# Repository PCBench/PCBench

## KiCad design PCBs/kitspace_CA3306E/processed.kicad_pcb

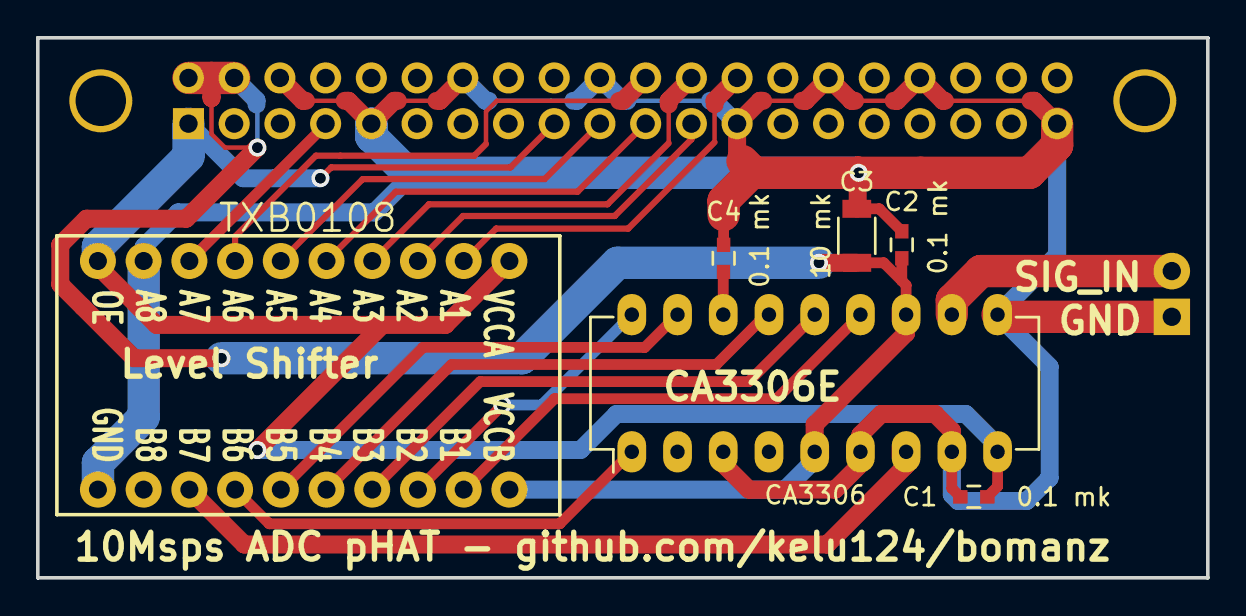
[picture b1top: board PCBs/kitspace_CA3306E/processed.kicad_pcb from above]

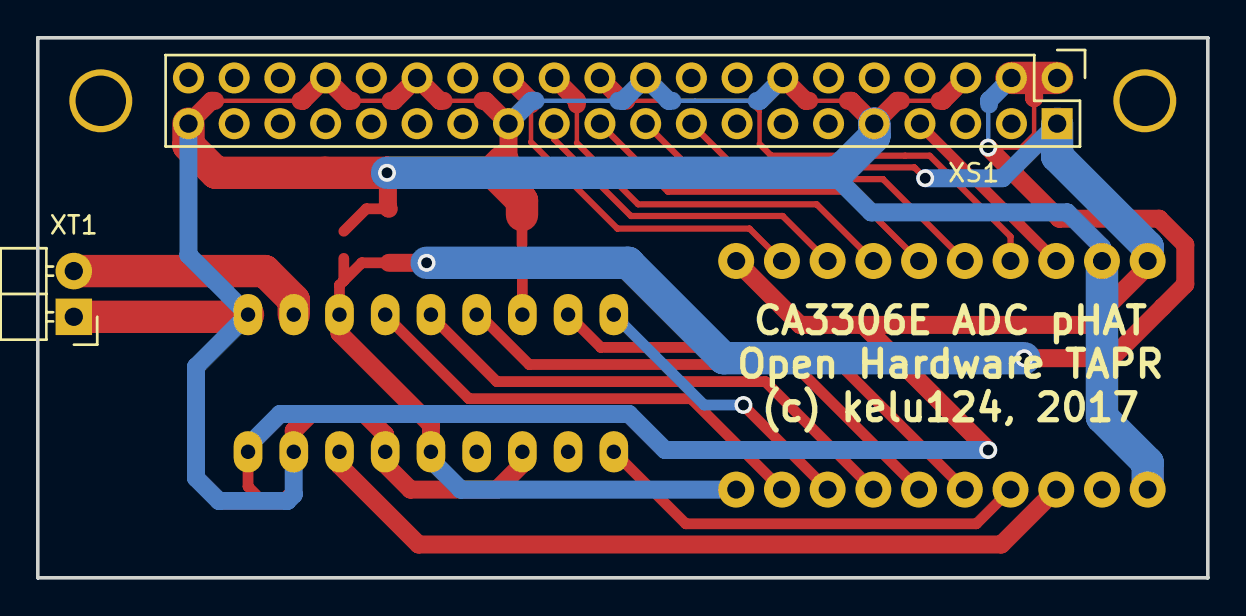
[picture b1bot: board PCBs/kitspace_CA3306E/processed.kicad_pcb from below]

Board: 2 copper layers, 65.0 x 30.0 mm, 8 parts (2 on the bottom side), 19 nets.

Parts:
C1, C2, C4: 0.1 mk; C_0603
C3: 10 mk; C_1206
CA3306: DIP-18_W7.62mm_LongPads
TXB0108: MountingHole_6mm_Pad
XS1: Pin_Header_Straight_2x20
XT1: Pin_Header_Angled_1x02

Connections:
B1: CA3306.13, TXB0108.19
B2: CA3306.14, TXB0108.17
B3: CA3306.15, TXB0108.16
B4: CA3306.17, TXB0108.15
B5: CA3306.18, TXB0108.18
B6: CA3306.1, TXB0108.14
C4_P: C4.1, CA3306.16
CLK: CA3306.7, TXB0108.13
GND: C1.2, C2.2, C3.2, C4.2, CA3306.3, CA3306.6, CA3306.8, CA3306.10, TXB0108.9, TXB0108.11, XS1.6, XS1.9, XS1.14, XS1.20, XS1.25, XS1.30, XS1.34, XS1.39, XT1.1
GPIO4: TXB0108.8, XS1.7
GPIO7: TXB0108.2, XS1.26
GPIO8: TXB0108.4, XS1.24
GPIO9: TXB0108.5, XS1.21
GPIO10: TXB0108.6, XS1.19
GPIO11: TXB0108.3, XS1.23
GPIO25: TXB0108.7, XS1.22
SIG_IN: CA3306.11, XT1.2
VDD_3V3: C1.1, CA3306.9, TXB0108.1, TXB0108.10, XS1.1, XS1.17
VDD_5V: C2.1, C3.1, CA3306.5, CA3306.12, TXB0108.20, XS1.2, XS1.4

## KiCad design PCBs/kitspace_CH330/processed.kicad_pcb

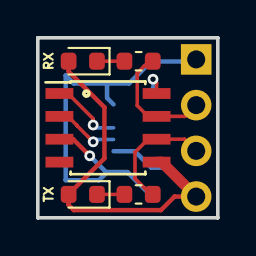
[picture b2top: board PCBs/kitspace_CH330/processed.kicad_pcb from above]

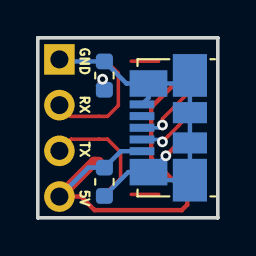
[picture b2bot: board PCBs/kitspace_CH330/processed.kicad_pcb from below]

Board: 2 copper layers, 10.0 x 10.0 mm, 9 parts (3 on the bottom side), 9 nets.

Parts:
C1, C2: 100n; C_0603_1608Metric
D1, D2: LED; LED_0603_1608Metric
J1: USB_B_Micro; USB_Micro-B_Molex_47346-0001
J2: Conn_01x04_Female; PinHeader_1x04_P2.54mm_Vertica_WITHOUT_SILK
R1, R2: 220; R_0603_1608Metric
U1: CH330; SOIC-8_3.9x4.9mm_P1.27mm

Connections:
/D+: J1.3, U1.1
/D-: J1.2, U1.2
/RXD: J2.2, R2.2, U1.7
/TXD: J2.3, R1.2, U1.6
/V3: C2.1, U1.8
GND: C1.2, C2.2, J1.5, J1.6, J2.1, U1.3
unnamed: D1.1, R1.1
unnamed: D2.1, R2.1
VBUS: C1.1, D1.2, D2.2, J1.1, J2.4, U1.5

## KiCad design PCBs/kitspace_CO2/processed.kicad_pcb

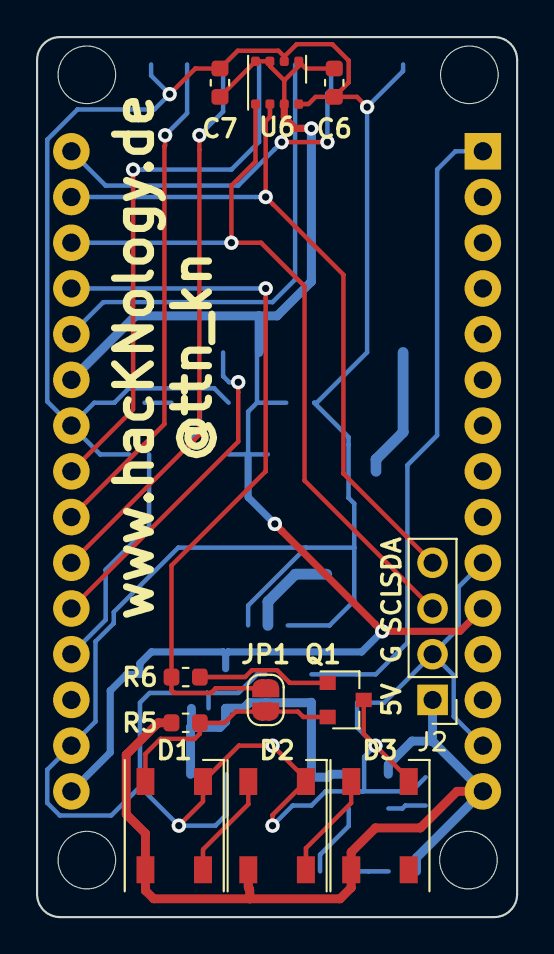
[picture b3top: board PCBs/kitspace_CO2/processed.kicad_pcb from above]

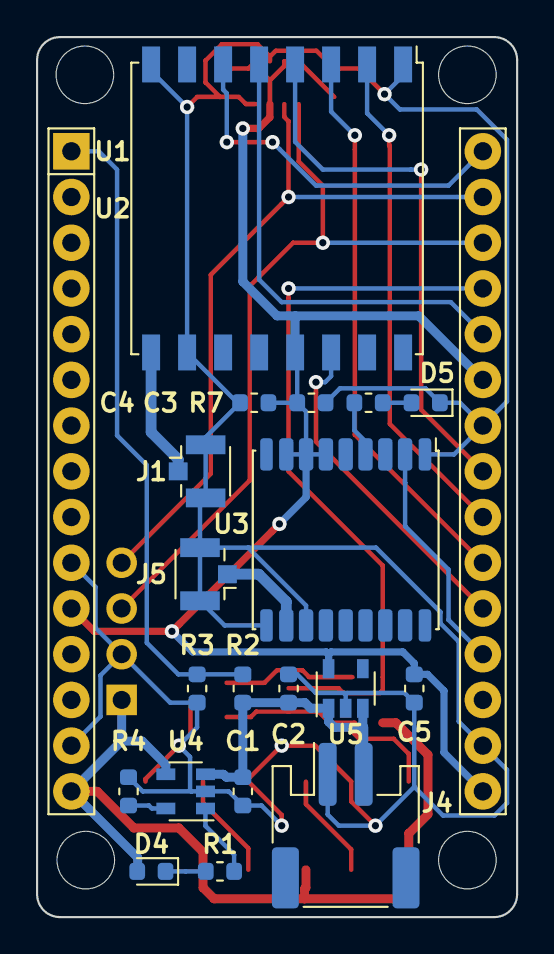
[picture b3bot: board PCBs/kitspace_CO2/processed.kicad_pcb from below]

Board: 2 copper layers, 26.7 x 48.9 mm, 31 parts (20 on the bottom side), 26 nets.

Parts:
C1, C3, C4, C5, C6, C7: 100n; C_0603_1608Metric
C2: 10µF; C_0603_1608Metric
D1, D2, D3: WS2812B; LED_WS2812B_PLCC4_5.0x5.0mm_P3.2mm
D4, D5: LED; LED_0603_1608Metric
J1, J5: Conn_Coaxial; U.FL_Hirose_U.FL-R-SMT-1_Vertical
J2: Display; PinHeader_1x04_P2.54mm_Vertical
J4: JST; JST_PH_S2B-PH-SM4-TB_1x02-1MP_P2.00mm_Horizontal
JP1: Jumper_NC_Small; SolderJumper-2_P1.3mm_Open_RoundedPad1.0x1.5mm
Q1: Q_NPN_BCE; SOT-23
R1, R2, R3, R5, R6, R7: 1k; R_0603_1608Metric
R4: 2k; R_0603_1608Metric
U1: NodeMCU1.0(ESP-12E); NodeMCU_Amica
U2: RFM95W-868S2; HOPERF_RFM9XW_SMD
U3: MAX-8Q; ublox_MAX
U4: MCP73831-2-OT; SOT-23-5
U5: AP2112K-3.3; SOT-23-5
U6: BME680; Bosch_LGA-8_3x3mm_P0.8mm_ClockwisePinNumbering

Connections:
+3V3: C3.2, C4.2, C5.2, C6.2, C7.2, U1.11, U1.16, U1.25, U2.13, U3.6, U3.7, U3.8, U5.5, U6.2, U6.5, U6.6, U6.8
+5V: D1.1, D2.1, D3.1, D4.2, J2.1, R5.2, U1.15, U4.4
+BATT: C1.2, C2.2, J4.2, R2.1, U4.3, U5.1, U5.3
A0: R2.2, R3.1, U1.1
CIPO: U1.22, U2.2
CLK: U1.23, U2.4
COPI: U1.21, U2.3
CS: U1.26, U2.5
GND: C1.1, C2.1, C3.1, C4.1, C5.1, C6.1, C7.1, D1.3, D2.3, D3.3, D5.1, J1.2, J2.2, J4.1, J5.2, Q1.3, R3.2, R4.2, U1.10, U1.14, U1.17, U1.24, U2.1, U2.8, U2.10, U3.1, U3.10, U3.12, U4.2, U5.2, U6.1, U6.7
IRQ: U1.20, U2.14
LED: JP1.1, R6.1, U1.27
unnamed: D1.2, D2.4
unnamed: D1.4, JP1.2, Q1.2, R5.1
unnamed: D2.2, D3.4
unnamed: D4.1, R1.1
unnamed: D5.2, R7.2
unnamed: J1.1, U2.9
unnamed: J5.1, U3.11
unnamed: Q1.1, R6.2
unnamed: R1.2, U4.1
unnamed: R4.1, U4.5
unnamed: R7.1, U3.4
RST: U1.30, U2.6
RXD: U1.19, U3.2
SCL: J2.3, U1.28, U6.4
SDA: J2.4, U1.29, U6.3

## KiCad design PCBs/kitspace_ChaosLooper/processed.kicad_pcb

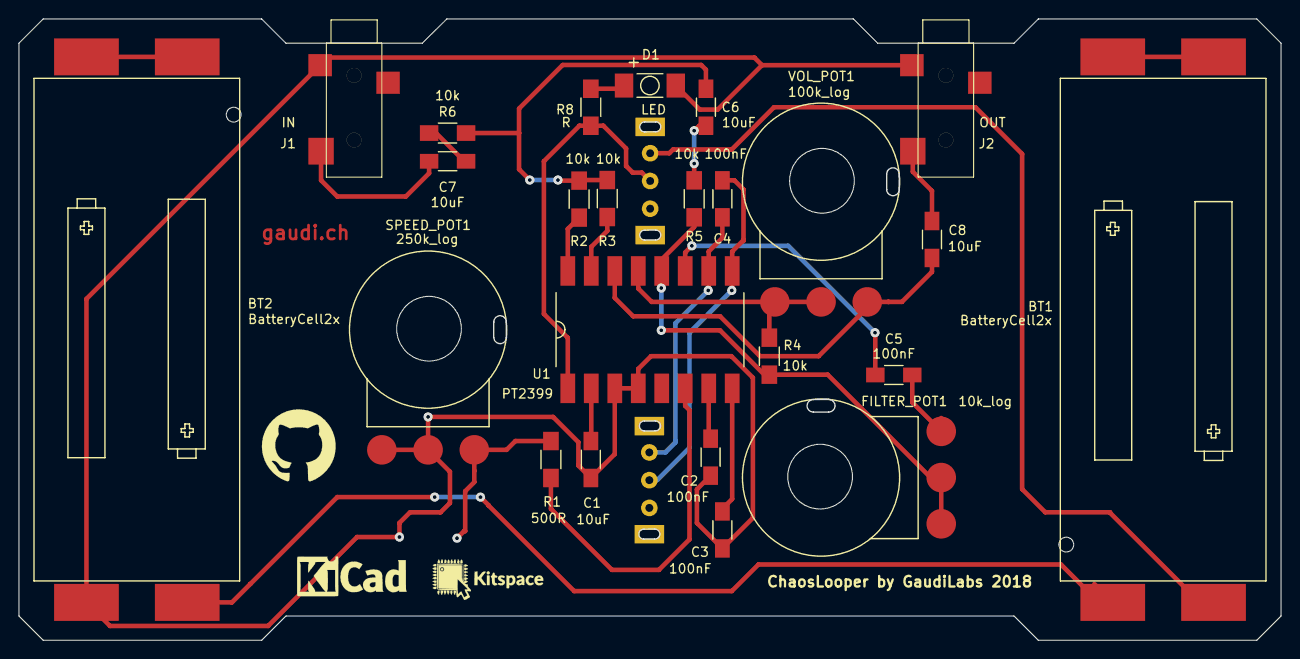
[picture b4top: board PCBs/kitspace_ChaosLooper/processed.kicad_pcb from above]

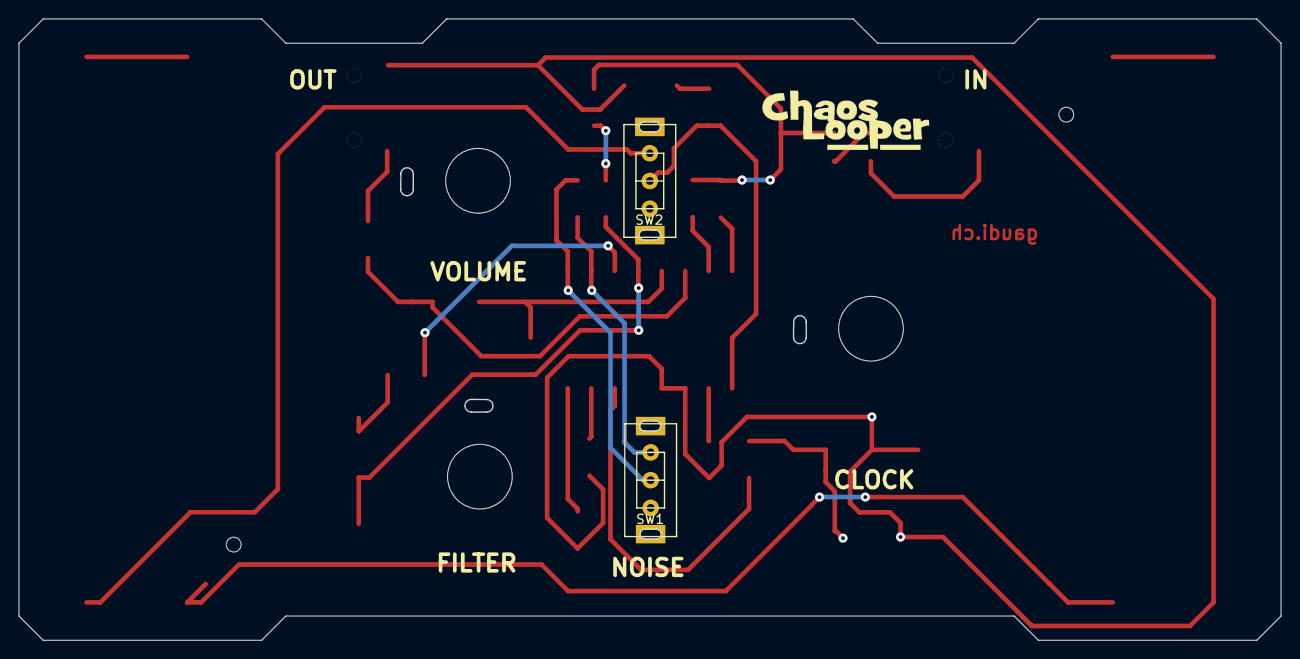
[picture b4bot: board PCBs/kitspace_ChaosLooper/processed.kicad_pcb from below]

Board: 2 copper layers, 136.5 x 67.2 mm, 26 parts (5 on the bottom side), 26 nets.

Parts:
BT1, BT2: BatteryCell2x; BAT_HOLDER_AAA_DOUBLE
C1, C6, C7, C8: 10uF; C_1206_HandSoldering
C2, C3, C4, C5: 100nF; C_1206_HandSoldering
D1: LED; TOPLED_R
FILTER_POT1: 10k_log; POTI_PCB
J1: IN; PLUG3_5_SwitchCraft_2B
J2: OUT; PLUG3_5_SwitchCraft_2B
R1: 500R; R_1206_HandSoldering
R2, R3, R4, R5, R6: 10k; R_1206_HandSoldering
R8: R; R_1206_HandSoldering
SPEED_POT1: 250k_log; POTI_PCB
SW1, SW2: Switch; SWITCH_SLIDE
U1: PT2399; DIL16_SMD
VOL_POT1: 100k_log; POTI_PCB

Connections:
GND: BT2.4, C1.2, C2.1, C3.1, D1.1, J1.1, J2.1, SPEED_POT1.2, SPEED_POT1.3, U1.3, U1.4
unnamed: BT1.1, BT1.4
unnamed: BT1.2, BT2.1
unnamed: BT1.3, SW2.1
unnamed: BT2.2, BT2.3
unnamed: C1.1, U1.2
unnamed: C2.2, U1.7
unnamed: C3.2, U1.8
unnamed: C4.1, SW1.2, U1.9
unnamed: C4.2, SW1.1, U1.10
unnamed: C5.1, FILTER_POT1.1
unnamed: C5.2, U1.11
unnamed: C6.1, R2.1, R3.1, R6.2
unnamed: C6.2, R5.1
unnamed: C7.1, J1.3
unnamed: C7.2, R6.1
unnamed: C8.1, J2.3
unnamed: C8.2, U1.14, VOL_POT1.1
unnamed: D1.2, R8.1
unnamed: FILTER_POT1.2, FILTER_POT1.3, R4.1, R5.2, U1.12
unnamed: R1.1, SPEED_POT1.1
unnamed: R1.2, U1.6
unnamed: R2.2, U1.16
unnamed: R3.2, U1.15
unnamed: R4.2, U1.13, VOL_POT1.2, VOL_POT1.3
VCC: R8.2, SW2.2, U1.1

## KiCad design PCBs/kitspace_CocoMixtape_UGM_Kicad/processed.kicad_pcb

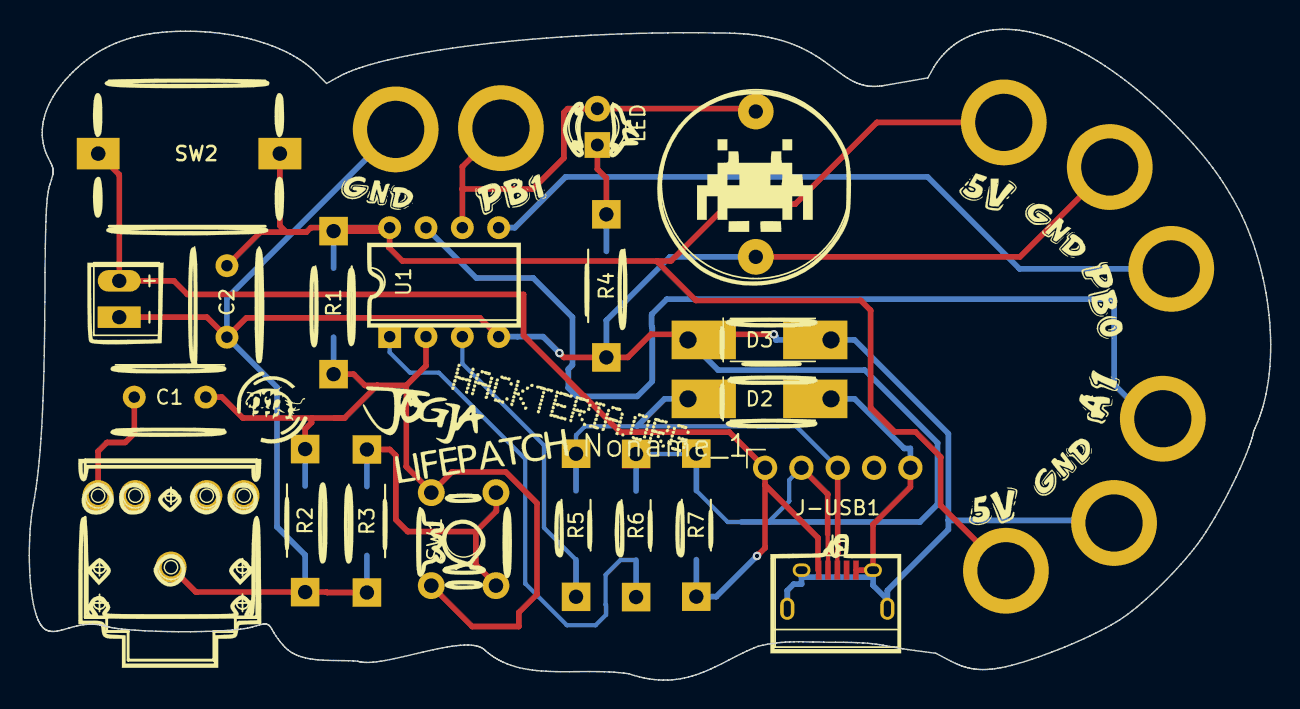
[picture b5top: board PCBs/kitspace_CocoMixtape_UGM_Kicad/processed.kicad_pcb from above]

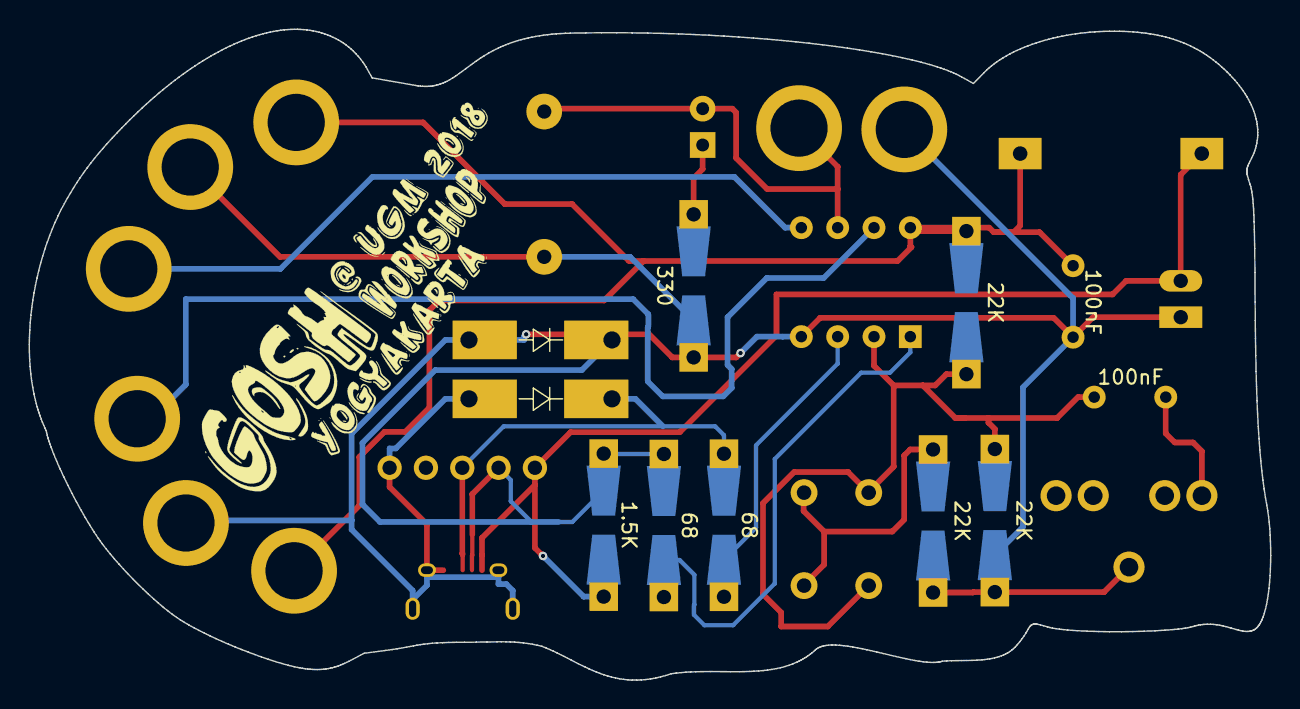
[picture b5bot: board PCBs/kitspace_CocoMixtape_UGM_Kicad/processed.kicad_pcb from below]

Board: 2 copper layers, 86.8 x 45.5 mm, 30 parts (9 on the bottom side), 14 nets.

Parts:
BT1: Battery_Cell; Bat_connector+-
C1, C2: 100nF; Capacitor
Coconut: LOGO; Coconut_Logo_small_Mask
D1: LED; LED_D3.0mm_FlatTop
D2, D3: D_Zener 3.3V; D_Zener_handsoldering
J1: JACK_TRS_6PINS; AUDIO-JACK-KIT_renamedPins
J2, J3, J4: CONN_01X01; Lock_Aligator
J5: USB_OTG; USB_Micro-B
J-USB1: CONN_01X05; Socket_Strip_USB
J_Aligator1, J_Aligator2, J_Aligator3, J_Aligator4, J_Aligator5: CONN_01X01; Lock_Aligator
LS1: Speaker; BUZZER
Noname_1: Silk_weird
R1, R2, R3: 22K; Resistor_SMD+THTuniversal
R4: 330; Resistor_SMD+THTuniversal
R5, R6: 68; Resistor_SMD+THTuniversal_OneSided
R7: 1.5K; Resistor_SMD+THTuniversal_OneSided
SW1: SW_Push; TACTILE-PTH_6mm
SW2: SW_SPST; Push_SWITCH-Square
U1: ATTINY85-20PU; DIP-8_W7.62mm

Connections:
+5V: BT1.1, J5.1, J-USB1.1, R7.1, SW2.1
GND: BT1.2, C2.2, D2.2, D3.2, J1.1, J5.5, J5.6, J-USB1.5, J_Aligator3.1, J_Aligator4.1, J_Aligator5.1, LS1.2, R2.2, R3.2, R4.1, U1.4
unnamed: C1.1, R1.2, R2.1, SW1.1, U1.2
unnamed: C1.2, J1.3
unnamed: D1.1, R4.2
unnamed: D1.2, J2.1, LS1.1, U1.6
unnamed: D2.1, J5.3, J-USB1.3, R5.2
unnamed: D3.1, J5.2, J-USB1.2, R6.2, R7.2
unnamed: J3.1, U1.7
unnamed: J4.1, U1.5
unnamed: R3.1, SW1.2
PB4: R5.1, U1.3
PB5: R6.1, U1.1
VCC: C2.1, J_Aligator1.1, J_Aligator2.1, R1.1, SW2.2, U1.8

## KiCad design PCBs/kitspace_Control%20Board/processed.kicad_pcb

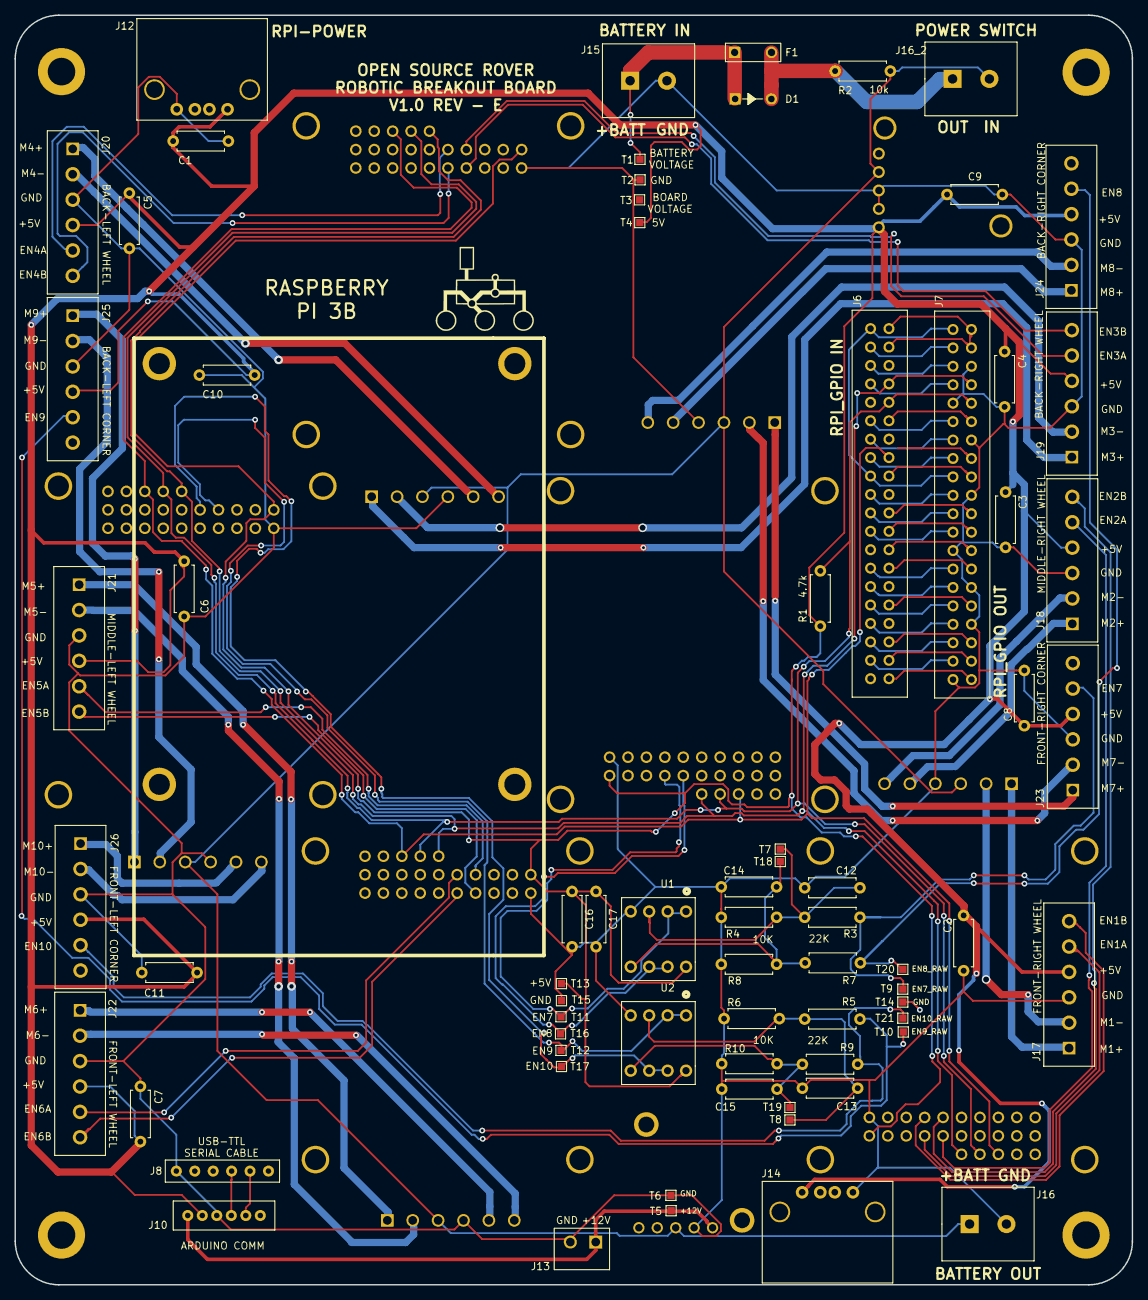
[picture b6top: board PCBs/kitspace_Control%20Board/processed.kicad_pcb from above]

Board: 2 copper layers, 154.0 x 175.0 mm, 90 parts (0 on the bottom side), 82 nets.

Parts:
C1: 0.1mF; R_Axial_DIN0207_L6.3mm_D2.5mm_P7.62mm_Horizontal
C2, C3, C4, C5, C6, C7, C8, C9, C10, C11, C16, C17: 100nf; R_Axial_DIN0207_L6.3mm_D2.5mm_P7.62mm_Horizontal
C12, C13, C14, C15: 100nF; R_Axial_DIN0207_L6.3mm_D2.5mm_P7.62mm_Horizontal
D1: D; 497-2738-5-ND
F1: Fuse; 507-1937-1-ND
J1, J2, J3, J4, J5: ED2627-ND
J6, J7: S9175-ND
J8: 6posheader; 6x1 Header Pin 0.1 Pitch
J9: S7038-ND
J10: 6posheader; 455-1708-ND
J11: S7038-ND; D24V22F12 Regulator
J12, J14: ED2989-ND-USB; ED2989-ND USB Conn
J13: ED1501-ND
J15, J16, J16_2: ED2580-ND
J17, J18, J19, J20, J21, J22, J23, J24, J25, J26: ED2744-ND
M1: Mounting_Holes; Raspberry pi footprint
MH1, MH2, MH3, MH4: #6THRU-HOLE
R1: 4.7K; R_Axial_DIN0207_L6.3mm_D2.5mm_P7.62mm_Horizontal
R2, R4, R6, R8, R10: 10K; R_Axial_DIN0207_L6.3mm_D2.5mm_P7.62mm_Horizontal
R3, R5, R7, R9: 22K; R_Axial_DIN0207_L6.3mm_D2.5mm_P7.62mm_Horizontal
RC1, RC2, RC3, RC4, RC5: RoboClaw; Roboclaw Mount
T1, T2, T3, T4, T5, T6, T7, T8, T9, T10, T11, T12, T13, T14, T15, T16, T17, T18, T19, T20, T21: test_point; TestPoint_Pad_1.0x1.0mm
U1, U2: LM358-N; AE9986-ND
y1: rover_silkscreen; rover_image

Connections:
+5V: C1.1, C2.1, C3.1, C4.1, C5.1, C6.1, C7.1, C8.1, C9.1, C10.1, C11.1, C16.1, C17.1, J9.5, J10.2, J12.1, J14.1, J17.4, J18.4, J19.4, J20.4, J21.4, J22.4, J23.4, J24.4, J25.4, J26.4, R1.2, RC1.1, RC2.1, RC3.1, RC4.1, RC5.1, T4.1, T13.1, U1.8, U2.8
+12V: J10.1, J11.5, J13.1, T5.1
+BATT: J1.3, J2.3, J3.3, J4.3, J5.3, J9.2, J11.3, J16.1, J16_2.2, R2.2
/3.3V: J6.1, J6.17, J7.1, J7.17
/E_STOP: J6.16, RC1.23, RC2.23, RC3.23, RC4.23, RC5.23
/GPIO05: J6.29, J7.29
/GPIO06: J6.31, J7.31
/GPIO12: J6.32, J7.32
/GPIO13: J6.33, J7.33
/GPIO16: J6.36, J7.36
/GPIO19: J6.35, J7.35
/GPIO20: J6.38, J7.38
/GPIO21: J6.40, J7.40
/GPIO26: J6.37, J7.37
/GPIO_CLK: J6.7, J7.7
/GPIO_GEN0: J6.11, J7.11
/GPIO_GEN1: J6.12, J7.12
/GPIO_GEN2: J6.13, J7.13
/GPIO_GEN3: J6.15, J7.15
/GPIO_GEN5: J6.18, J7.18
/GPIO_GEN6: J6.22, J7.22
/GPI_CE1_N: J6.26, J7.26
/I2C_ID1: J6.27, J7.27
/I2C_ID2: J6.28, J7.28
/PI_5V: J6.2, J6.4, J7.2, J7.4
/RC1EN1A: J17.5, RC1.7
/RC1EN1B: J17.6, RC1.8
/RC1EN2A: J18.5, RC1.9
/RC1EN2B: J18.6, RC1.10
/RC1M1A: J1.1, J17.1
/RC1M1B: J1.2, J17.2
/RC1M2A: J1.5, J18.1
/RC1M2B: J1.6, J18.2
/RC2EN1A: J19.5, RC2.7
/RC2EN1B: J19.6, RC2.8
/RC2EN2A: J20.5, RC2.9
/RC2EN2B: J20.6, RC2.10
/RC2M1A: J2.1, J19.1
/RC2M1B: J2.2, J19.2
/RC2M2A: J2.5, J20.1
/RC2M2B: J2.6, J20.2
/RC3EN1A: J21.5, RC3.7
/RC3EN1B: J21.6, RC3.8
/RC3EN2A: J22.5, RC3.9
/RC3EN2B: J22.6, RC3.10
/RC3M1A: J3.1, J21.1
/RC3M1B: J3.2, J21.2
/RC3M2A: J3.5, J22.1
/RC3M2B: J3.6, J22.2
/RC4EN1A: RC4.7, T11.1, U1.1, U1.2
/RC4EN1A_RAW: J23.5, R3.1, T9.1
/RC4EN2A: RC4.9, T16.1, U1.6, U1.7
/RC4EN2A_RAW: J24.5, R7.1, T20.1
/RC4M1A: J4.1, J23.1
/RC4M1B: J4.2, J23.2
/RC4M2A: J4.5, J24.1
/RC4M2B: J4.6, J24.2
/RC5EN1A: RC5.7, T12.1, U2.1, U2.2
/RC5EN1A_RAW: J25.5, R5.1, T10.1
/RC5EN2A: RC5.9, T17.1, U2.6, U2.7
/RC5EN2A_RAW: J26.5, R9.1, T21.1
/RC5M1A: J5.1, J25.1
/RC5M1B: J5.2, J25.2
/RC5M2A: J5.5, J26.1
/RC5M2B: J5.6, J26.2
/RXD: J6.10, J7.10, R1.1, RC1.22, RC2.22, RC3.22, RC4.22, RC5.22
/SCL1: J6.5, J7.5
/SDA1: J6.3, J7.3
/SPI_CEO_N: J6.24, J7.24
/SPI_CLK: J6.23, J7.23
/SPI_MISO: J6.21, J7.21
/SPI_MOSI: J6.19, J7.19
/TTL_RXD: J8.5, J10.5
/TTL_TXD: J8.4, J10.4
/TXD: J6.8, J7.8, RC1.21, RC2.21, RC3.21, RC4.21, RC5.21
GND: C1.2, C2.2, C3.2, C4.2, C5.2, C6.2, C7.2, C8.2, C9.2, C10.2, C11.2, C12.1, C13.1, C14.1, C15.1, C16.2, C17.2, J1.4, J2.4, J3.4, J4.4, J5.4, J7.6, J7.9, J7.14, J7.20, J7.25, J7.30, J7.34, J7.39, J8.1, J9.3, J9.4, J10.3, J11.4, J12.4, J13.2, J14.4, J15.2, J16.2, J17.3, J18.3, J19.3, J20.3, J21.3, J22.3, J23.3, J24.3, J25.3, J26.3, R4.2, R6.2, R8.2, R10.2, RC1.2, RC2.2, RC3.2, RC4.2, RC5.2, T2.1, T6.1, T15.1, U1.4, U2.4
unnamed: C12.2, R3.2, R4.1, T7.1, U1.3
unnamed: C13.2, R5.2, R6.1, T8.1, U2.3
unnamed: C14.2, R7.2, R8.1, T18.1, U1.5
unnamed: C15.2, R9.2, R10.1, U2.5
unnamed: D1.1, F1.1, J15.1, T1.1
unnamed: D1.2, F1.2, J16_2.1, R2.1

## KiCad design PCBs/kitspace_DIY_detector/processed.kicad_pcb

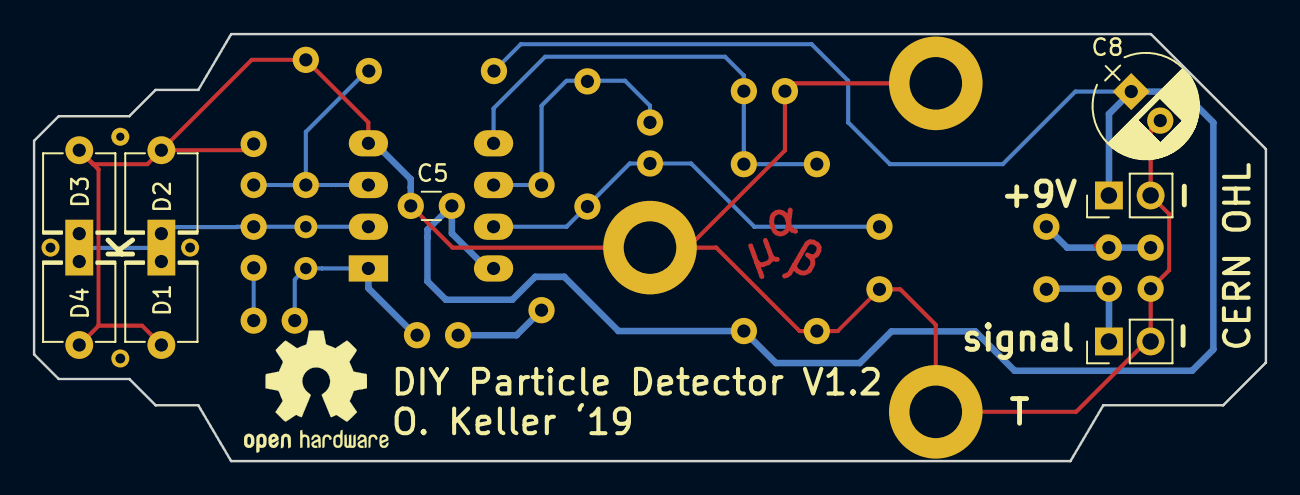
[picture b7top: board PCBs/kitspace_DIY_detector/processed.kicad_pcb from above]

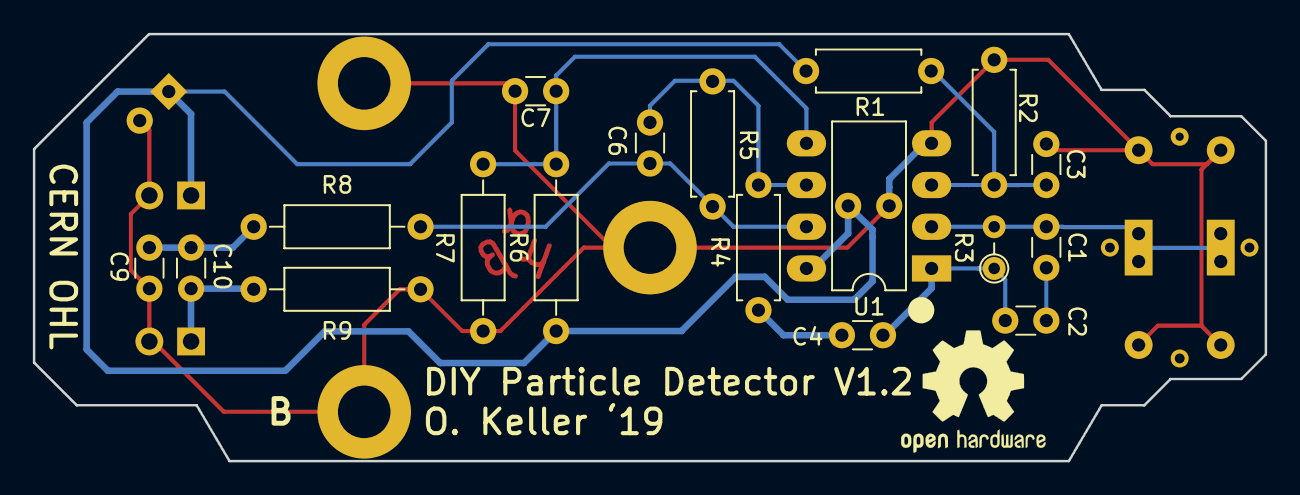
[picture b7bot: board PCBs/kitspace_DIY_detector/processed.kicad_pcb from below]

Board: 2 copper layers, 75.0 x 26.0 mm, 33 parts (18 on the bottom side), 12 nets.

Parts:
C1, C2: 10p; C_Disc_D3.0mm_W1.6mm_P2.50mm
C3, C5, C7, C10: 100n; C_Disc_D3.0mm_W1.6mm_P2.50mm
C4: 470n; C_Disc_D3.0mm_W1.6mm_P2.50mm
C6: 3n3; C_Disc_D3.0mm_W1.6mm_P2.50mm
C8: 47u; CP_Radial_D6.3mm_P2.50mm
C9: 6n8; C_Disc_D3.0mm_W1.6mm_P2.50mm
D1: BPX61; PhotoDiode_DIL2_4.3x4.65_RM5.08
D2, D3, D4: DNP; PhotoDiode_DIL2_4.3x4.65_RM5.08
J1, J2: Conn_01x02_Female; Pin_Header_Straight_1x02_Pitch2.54mm
MK1, MK2, MK3, MK4: via for coincidence sandwich; SolderWirePad_single_0-8mmDrill
MK5, MK6, MK7: M3 support; MountingHole_3.2mm_M3_ISO7380_Pad
R1, R4: 4k7; R_Axial_DIN0207_L6.3mm_D2.5mm_P7.62mm_Horizontal
R2: 15k; R_Axial_DIN0207_L6.3mm_D2.5mm_P7.62mm_Horizontal
R3: 40M; R_Axial_DIN0204_L3.6mm_D1.6mm_P2.54mm_Vertical
R5: 1M; R_Axial_DIN0207_L6.3mm_D2.5mm_P7.62mm_Horizontal
R6, R7, R8: 10k; R_Axial_DIN0207_L6.3mm_D2.5mm_P10.16mm_Horizontal
R9: 2k2; R_Axial_DIN0207_L6.3mm_D2.5mm_P10.16mm_Horizontal
U1: TLE2072; DIP-8_W7.62mm_LongPads

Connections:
+9V: C5.1, C8.1, J1.1, R1.1, R6.1, U1.8
/Output: C10.2, J2.1, R9.1
GND: C3.2, C5.2, C7.2, C8.2, C9.2, D1.2, D2.2, D3.2, D4.2, J1.2, J2.2, MK5.1, MK6.1, MK7.1, R2.2, R7.2, R9.2, U1.4
unnamed: C1.1, D1.1, D2.1, D3.1, D4.1, R3.2, U1.2
unnamed: C1.2, C2.1
unnamed: C2.2, C4.1, R3.1, U1.1
unnamed: C3.1, R1.2, R2.1, U1.3
unnamed: C4.2, R4.2
unnamed: C6.1, R4.1, R5.2, U1.6
unnamed: C6.2, R5.1, R8.1, U1.7
unnamed: C7.1, R6.2, R7.1, U1.5
unnamed: C9.1, C10.1, R8.2

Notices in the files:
PCBs/kitspace_DIY_detector/processed.kicad_pcb:
CERN open hardware license V1.2
CERN OHL
